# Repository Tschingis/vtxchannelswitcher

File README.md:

# VTX Channel Switcher

This project is a nice little helper for people who are using video transmitters in quadrocopters or other remote controlled vehicles with a VTX. It allows to switch the video channel of a unify vtx with the attached remote control utilising a rc channel. It consists of a hardware part which connects the rc channel to the unify vtx and a lua script extension for the wide spread taranis remote control to setup the vtx channel.

## Features

* Switches VTX channel between race band 1 to 8
* Security feature to disallow channel change after a predefined timeout after powerup
* LUA Gui script for FrSky Taranis

## Restrictions

* Works currently only with unify vtx with smartaudio support (V1 or V2) (tested Unify 5.8 Pro HV)
* Might not work with connected microphone on audio pin, since a cheap voltage divider (5V to 3.3V) is used to interface the unify. (Maybe someone tests this). The board could be easily changed to run directly from a 3.3V power supply, when available, so no voltage divider is needed.
* LUA Script works only with OpenTX remotes (Taranis tested), but the vtx channel switcher can also be controlled with a poti on the remote control.

## Required Knowledge

If you want to build such a device yourself you should be familar with arduino ide and programming mcus utilising the ISP interface, although i will try to explain the most parts or link needed tutorials. In addition you should know how to solder mcus or in general electronics.

## Required Tools

In order to build a VTX channel switcher you need the following tools

* Solder iron
* Any arduino supported Atmel ISP Programmer (i.e. USBAsp or ArduinoISP)
* Required parts for the circuit (found in circuit, ATTiny13A MCU,some resistors and a capacitor)
* Multimeter with frequency measurement (not always needed)

## Building the Hardware

The interface between the rc receiver (or flight controller) and the unify vtx is a rather simple circuit which consist mainly of an ATTiny13A. This mcu is very low cost and needs nearly no additional parts to run reliable. The pcb is found in the circuit folder. You can use the provided pcb which uses SMD parts or you can just build your own version with DIP parts from the schematic. The required VCC is 5V.

## Building the MCU Software 

The software for the MCU is build with arduino since its easy to install and use. So install the following software

* [Arduino IDE 1.6](https://www.arduino.cc/)
* ATTiny13 Core for arduino 1.6 [Core13](https://sourceforge.net/projects/ard-core13/?source=navbar)  the version *core13_022_arduino_1_6.zip*. Installation is done by unzipping the downloaded file and then put the folder *attiny13* into *Your User/documents/Arduino/hardware*. If the directory should not exist, create it.

After the installation of the Arduino IDE and the required ATTiny13 Core you should start the Arduino IDE and check if the ATTiny13 can be select as a board. 

If everything went ok, you should select the board *Attiny 13A standalone 1.2mhz*. Now open the arduino project which can be found in the channelswitcher directory. The sketch should compile ok when you press the verify button. You are now ready to flash the mcu.

## Flashing the ATTiny

Flashing a standalone attiny is not as comfortable as most arduino boards since you have to use the Atmel ISP interface of the mcu to flash it. In order to use the ISP you have to connect the ISP programmer to the attiny. The supplied pcb layout does not provide any solder points to connect the ISP lines to the attiny. You should just solder some cables directly to the mcu pins for programming (or if you are using a DIP part you could use a socket) which will be removed afterwards. I will not go into too much detail of how to connect the ISP to the attiny13 as there are many tutorials out there which show how to connect it. The attiny13 is pin compatible (in respect to ISP) with the attiny45/85 so you can also use a tutorial for these MCUs on how to wire up the MCU against the ISP. If you are using an ArduinoISP the wiring would be 

* Arduino +5V      --->  ATtiny Pin 8
* Arduino Ground --->  ATtiny Pin 4
* Arduino Pin 10   --->  ATtiny Pin 1
* Arduino Pin 11    --->  ATtiny Pin 5
* Arduino Pin 12    --->  ATtiny Pin 6
* Arduino Pin 13    --->  ATtiny Pin 7

When everything is connected and powered up you should be able to program the attiny by pressing the upload button in the arduino ide. If the programming fails, check the connections. Pin 1 on the attiny is marked with a small triangle on top. There should also be no connection between the isp connection wires (solder blobs etc.).

## Connecting the VTX Switcher to the Unify VTX

The connection to the unify vtx is rather simple since you have only to connect the audio cable from the unify with the smart audio pad of the vtx channel switcher.

## Setting up the Flight Controller for Channel Forwarding

The most common use-case for this project will be, that it is installed inside a copter which is controlled by a flight controller. Nowadays the most users have serial receiver installed which will not output the required servo signal for the vtx channel switcher. I will show for some flight controllers how to setup a channel forwarding which puts the required servo signal on a pwm output of the flight controller

### Setting up Betaflight/Cleanflight

Betaflight/Cleanflight has the possiblity to output a servo signal to the pwm(esc) pins. I tested it only with a RMDO board but it should apply to other boards as well. Betaflight can enable channel forwarding in the feature section of the configurator but this just leads to frustration as it does not activate all required features so just open the CLI and type

    feature CHANNEL_FORWARDING 
    feature SERVO_TILT
    save

Now you can setup a servo mapping in the configurator gui. On most F3 targets ESC pins 7-8 map to servo 0-1. The servo pane actually maps an input channel to a servo(ESC pin). Just set a checkbox on the input which should be used for the servo, i.e. check the box *A2* on *Servo 0*. Now you have mapped Aux2 input channel to ESC Pin 7 (servo0), the rest of the servo settings should be kept untouched.

### Setting up KISS FC

For the KISS FC its much easier (as supposed). In the AUX1-4 channel section you should just select one of the functions *PWM5: Servo Mid* or *PWM6: Servo Mid*. This maps the input from the selected AUX channel to the PWM5 or PWM6 output pin of the KISS FC.

## Setting up Taranis Channel Switcher LUA Script

The FrSky Taranis is a very nice radio with excellent software support. This allows us to put a LUA script on the Taranis (SD Card) and show a custom screen which modifies the model memory in order to send the correct servo signal for a specific video channel. 
The script actually computes a global variable value for GV1 (can be changed to any other if already used) which is then used inside a mixer to generate an usuable servo signal for the vtx channel switcher. 
The first step is to copy over the *channelselector.lua* script from the repository *opentx* directory to the sd card of the taranis. You can put it anythere on the sd card, but you should use the root of the card since there will be no shortcut (switch assignment) to the script and you have to navigate to the script in the sd card browser of the taranis. 
The next step is to create a new mixer for the rc channel which has been mapped previously to the vtx channel switcher hw. Open the mixer settings and change the following values

    Source -> MAX
    Weight -> GV1  (long enter press on the weight allows to assign global variables)
    
## Starting the LUA Script

You can now start the *channelselector.lua* script when you are on the main screen of the taranis by a long press on the menu button and then go to the sd card browser (page btn). In the sd card browser navigate to the script and execute it (select it with enter and choose *Execute*). **Have Fun**

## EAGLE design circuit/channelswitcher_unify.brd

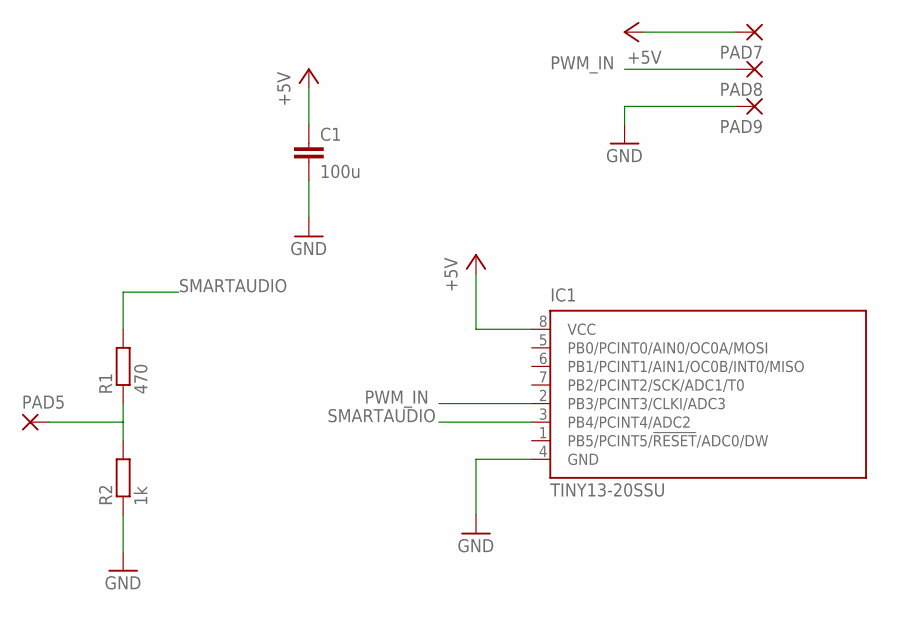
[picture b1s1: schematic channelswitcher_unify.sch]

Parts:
C1: 100u; C0805
IC1: TINY13-20SSU; 8S1
PAD5, PAD7, PAD8, PAD9: SMD2; SMD1,27-2,54
R1: 470; R0805
R2: 1k; R0805

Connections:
+5V: C1.1, IC1.8 (VCC), PAD7.1
GND: C1.2, IC1.4 (GND), PAD9.1, R2.1
unnamed: PAD5.1, R1.1, R2.2
PWM_IN: IC1.2 (PB3/PCINT3/CLKI/ADC3), PAD8.1
SMARTAUDIO: IC1.3 (PB4/PCINT4/ADC2), R1.2

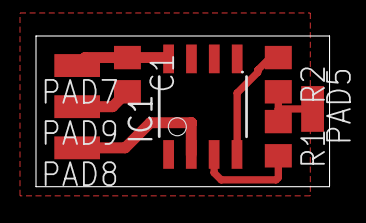
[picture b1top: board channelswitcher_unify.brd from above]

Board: 2 copper layers, 16.3 x 8.4 mm, 8 parts (0 on the bottom side), 5 nets.

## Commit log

2016-09-28 Add image of attiny13 board selection
2016-09-28 -added channel switcher arduino sketch
2016-09-28 -added image for board wiring
2016-09-28 -added servo mapping from bf configurator
2016-09-28 -added circuit and lua script
2016-09-28 correct spelling
2016-09-29 -added author
